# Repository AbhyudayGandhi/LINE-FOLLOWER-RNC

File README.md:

# LINE-FOLLOWER-RNC
Fastest Line Follower robot

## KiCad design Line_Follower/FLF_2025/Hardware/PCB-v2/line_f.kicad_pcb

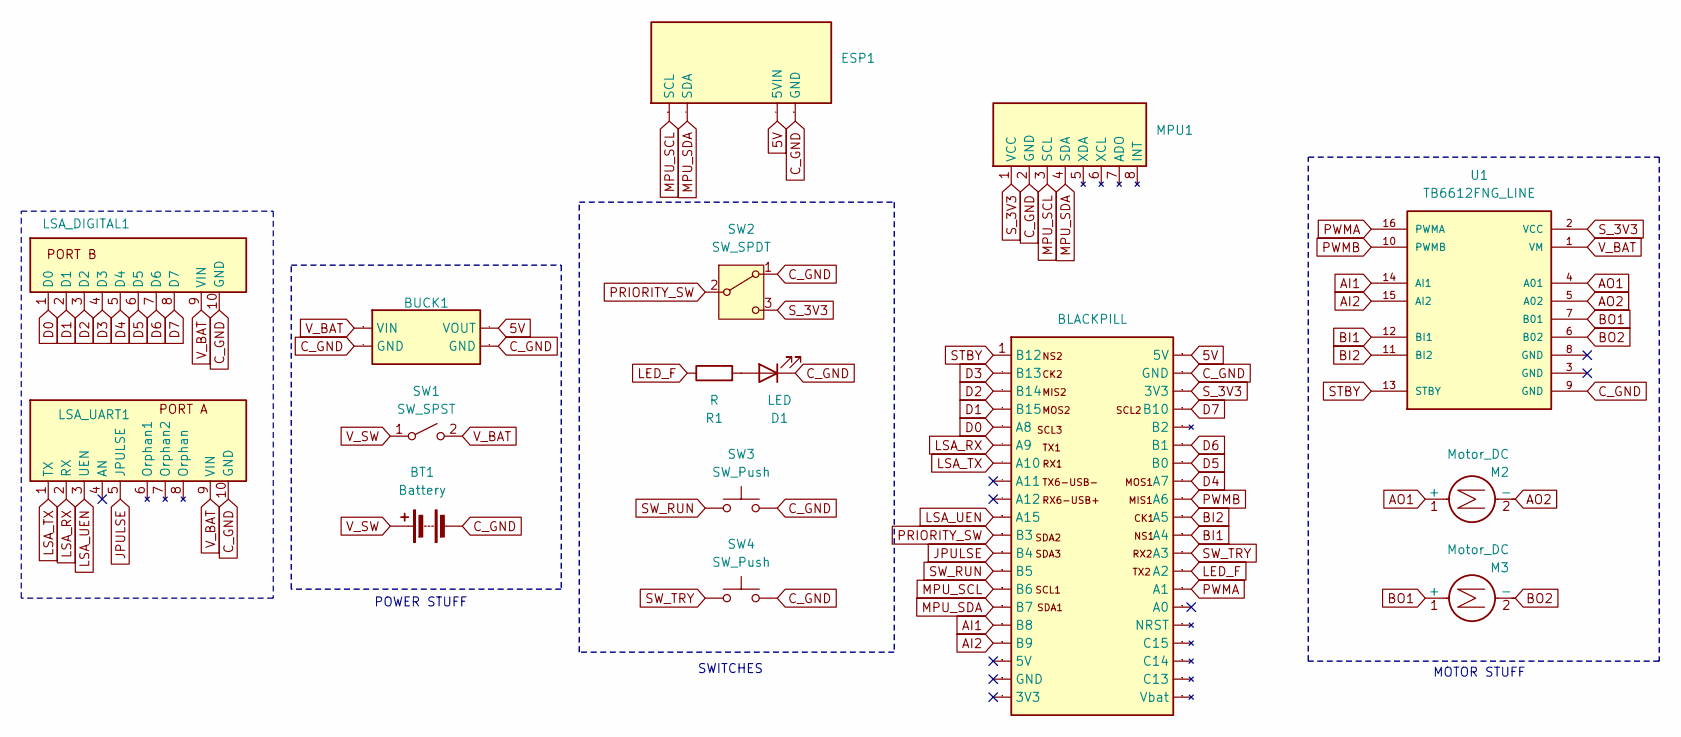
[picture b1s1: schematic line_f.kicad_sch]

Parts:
BT1: Battery; BATTERY_LINE_XT60
BUCK1: BUCK_SMD
D1: LED; LED_LINE
ESP1: 4pin
LSA_DIGITAL1: LSA_DIGITAL
LSA_UART1: LSA_UART
M2, M3: Motor_DC; connector_motor
MPU1: MPU6050_AR
R1: R; RESISTOR_LINE
SW1: SW_SPST; battery_sw
SW2: SW_SPDT; SLIDE SW
SW3, SW4: SW_Push; push_button
U1: TB6612FNG_LINE; PARTREV 11-13-17
m1: BLACKPILL; FINAL_BLACKPILL_LINE; Manufacturer Part Black Pill V3

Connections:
5V: BUCK1.2 (VOUT), ESP1.3 (5VIN), m1.21 (5V)
AI1: U1.14 (AI1), m1.16 (B8)
AI2: U1.15 (AI2), m1.17 (B9)
AO1: M2.1 (+), U1.4 (A01)
AO2: M2.2 (-), U1.5 (A02)
BI1: U1.12 (BI1), m1.31 (A4)
BI2: U1.11 (BI2), m1.30 (A5)
BO1: M3.1 (+), U1.7 (B01)
BO2: M3.2 (-), U1.6 (B02)
C_GND: BT1.2 (-), BUCK1.3 (GND), BUCK1.4 (GND), D1.1 (K), ESP1.4 (GND), LSA_DIGITAL1.10 (GND), LSA_UART1.10 (GND), MPU1.2 (GND), SW2.1 (A), SW3.2, SW4.2, U1.9 (GND), m1.22 (GND)
D0: LSA_DIGITAL1.1 (D0), m1.5 (A8)
D1: LSA_DIGITAL1.2 (D1), m1.4 (B15)
D2: LSA_DIGITAL1.3 (D2), m1.3 (B14)
D3: LSA_DIGITAL1.4 (D3), m1.2 (B13)
D4: LSA_DIGITAL1.5 (D4), m1.28 (A7)
D5: LSA_DIGITAL1.6 (D5), m1.27 (B0)
D6: LSA_DIGITAL1.7 (D6), m1.26 (B1)
D7: LSA_DIGITAL1.8 (D7), m1.24 (B10)
JPULSE: LSA_UART1.5 (JPULSE), m1.12 (B4)
LED_F: R1.1, m1.33 (A2)
LSA_RX: LSA_UART1.2 (RX), m1.6 (A9)
LSA_TX: LSA_UART1.1 (TX), m1.7 (A10)
LSA_UEN: LSA_UART1.3 (UEN), m1.10 (A15)
MPU_SCL: ESP1.1 (SCL), MPU1.3 (SCL), m1.14 (B6)
MPU_SDA: ESP1.2 (SDA), MPU1.4 (SDA), m1.15 (B7)
unnamed: D1.2 (A), R1.2
PRIORITY_SW: SW2.2 (B), m1.11 (B3)
PWMA: U1.16 (PWMA), m1.34 (A1)
PWMB: U1.10 (PWMB), m1.29 (A6)
STBY: U1.13 (STBY), m1.1 (B12)
SW_RUN: SW3.1, m1.13 (B5)
SW_TRY: SW4.1, m1.32 (A3)
S_3V3: MPU1.1 (VCC), SW2.3 (C), U1.2 (VCC), m1.23 (3V3)
V_BAT: BUCK1.1 (VIN), LSA_DIGITAL1.9 (VIN), LSA_UART1.9 (VIN), SW1.2 (B), U1.1 (VM)
V_SW: BT1.1 (+), SW1.1 (A)

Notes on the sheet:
MOTOR STUFF
SWITCHES
POWER STUFF

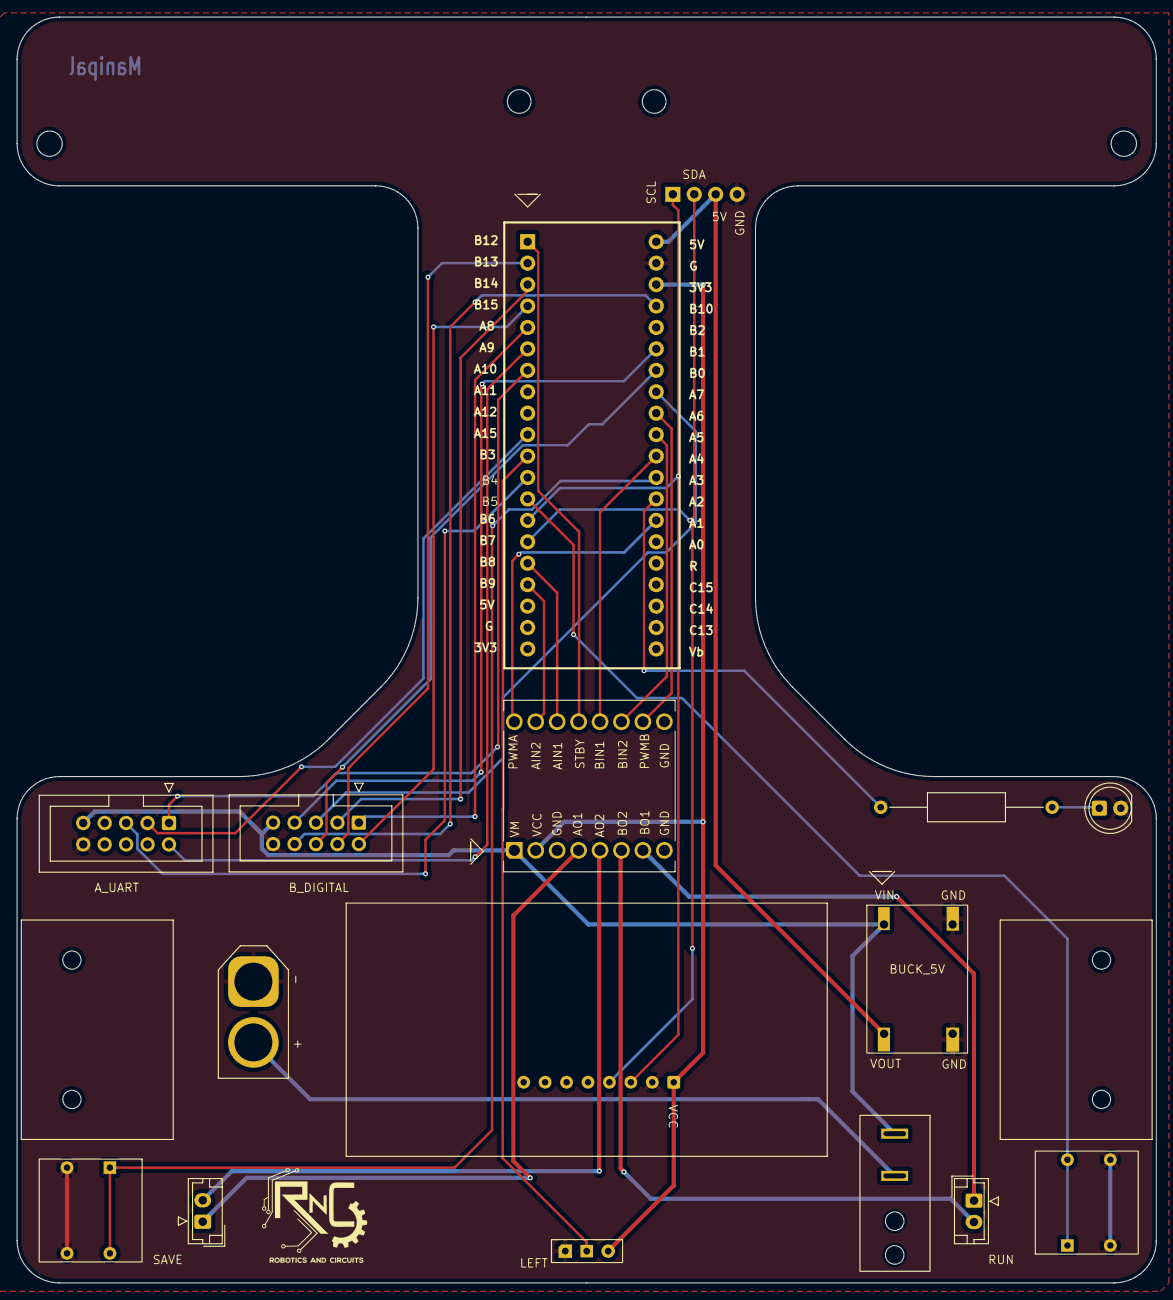
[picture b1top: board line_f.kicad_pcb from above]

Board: 2 copper layers, 135.0 x 150.0 mm, 16 parts (1 on the bottom side), 35 nets.
